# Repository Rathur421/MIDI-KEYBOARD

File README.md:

# 🎹 ARDUINO UNO BASED MIDI KEYBOARD WITH VELOCITY V0.1

The documentation of the code is currently being made as well as the code improved.

This project use the [Arduino MIDI Library](https://github.com/FortySevenEffects/arduino_midi_library)

:warning: the easiest way will always be to buy a midi-keyboard

Up to 88 Key(and more if needed) currently tested for 61 key without major issues.

This github repo is made to propose some (I hope) helpfull ressources to make a MIDI Keyboard wich take in charge the velocity using an arduino-uno and some multiplexer(74HC4051). This my first:

- ARDUINO based project.
- [ARDUINO library](https://github.com/Rathur421/MIDI-KEYBOARD/tree/Master/PCB/circuit) (and first C++ program).
- [PCB conception](https://github.com/Rathur421/MIDI-KEYBOARD/tree/Master/Arduino_Code/lib).

so please try to not be too rude.

The file for the arduino shield conception are [here](https://github.com/Rathur421/MIDI-KEYBOARD/tree/Master/PCB/circuit). The file were created using [Kicad](https://kicad.org/).

## How the shield works

The number of pin on an arduino is clearly not sufficient to plug directly a keyboard matrice of a large keyboard so the idea is to use some multiplexer/demultiplexer to help us.

The biggest problem of this basic idea is that the more key you had the longueur will be the execution of the loop and the less precise will be the velocity.

we use only 1 demultiplexer `READMUX` and up to 3 multiplexer `WRITE_MUX`.
They are globally define in the code ([here](https://github.com/Rathur421/MIDI-KEYBOARD/blob/Master/Arduino_Code/lib/VeloceKey/src/VeloceKey.cpp) line 4 and 6) as they are dependent of the architecture of the project.

The switch between the different multiplexer is made by activating the pin to which each of the multiplexer is link in the PCB(from pin 11 to 13 of the arduino uno board) in the [main] program (from line 23 to 30).

## How the code works

You need to initialise all the key of your actual keyboard and put it in an array as in [main][main] from line 60 and 130.

Then you update all the key and check if the state changed based on the method `YOUR_VELOCEKEY.getKeyChanged()`.
If the state changed you can do the following:

- If it is in state 2 you can send a `MIDI.sendNoteOn(YOUR_VELOCEKEY.getNote(), YOUR_VELOCEKEY.getVelocity(), 1);`.
- If it is in state 3 you can send a `MIDI.sendNoteOff(YOUR_VELOCEKEY.getNote(), YOUR_VELOCEKEY.getVelocity(), 1);`.

That is made in the function update in [main][main] from line 20 to 58.

The code use principally the library [VeloceKey](###well-how-does-the-veloceKey-library-works)

### Well how does the VeloceKey library works?

This library is made to be intuitive for the user as each physical key of the keyboard correspond to a VeloceKey object in the program.

The VeloceKey object is built around a state byte to take the less place possible of the 2kB of RAM available on the Arduino Uno.

| bit position | 7        | 6        | 5                    | 4                    | 3              | 2                       | 1          | 0                   |
| ------------ | -------- | -------- | -------------------- | -------------------- | -------------- | ----------------------- | ---------- | ------------------- |
| used for     | not used | not used | Key previous state 1 | Key previous state 2 | velocity state | velocity previous state | main state | main previous state |

The key of a midi keyboard is composed of two push button, the main and velocity button each one have his `actual` and `previous state` stored inside the `state byte`.

When the programme loop the `state byte` [update](####Update) and if the `previous state` doesn't match with the `actual state` then the `key state` will be changed.

#### Key state

The `key state` can be accessed via the method `YOUR_VELOCEKEY.getKeyState()` which return a byte between 0 and 3 which stand for:

- 0: Key not pressed
- 1: Key currently pressed
- 2: Key pressed
- 3: Key released

The `key state` is not directly stored inside the `byte state` as it can be deduced of the `key previous state` and the `velocity` and `main state`

#### Update

The update basically store the `key previous state` and replace the `previous state` by the `actual state` before storing the `new state` in the `actual state` if necessary.

If the `state` just passed to 1 the time is registered inside the `veloceKey` object.

If the `state` just passed to 2 the timer is used to store the velocity inside the `veloceKey` object and can be accessed with `YOUR_VELOCEKEY.getVelocity()`.

[main]: https://github.com/Rathur421/MIDI-KEYBOARD/blob/Master/Arduino_Code/src/main.cpp

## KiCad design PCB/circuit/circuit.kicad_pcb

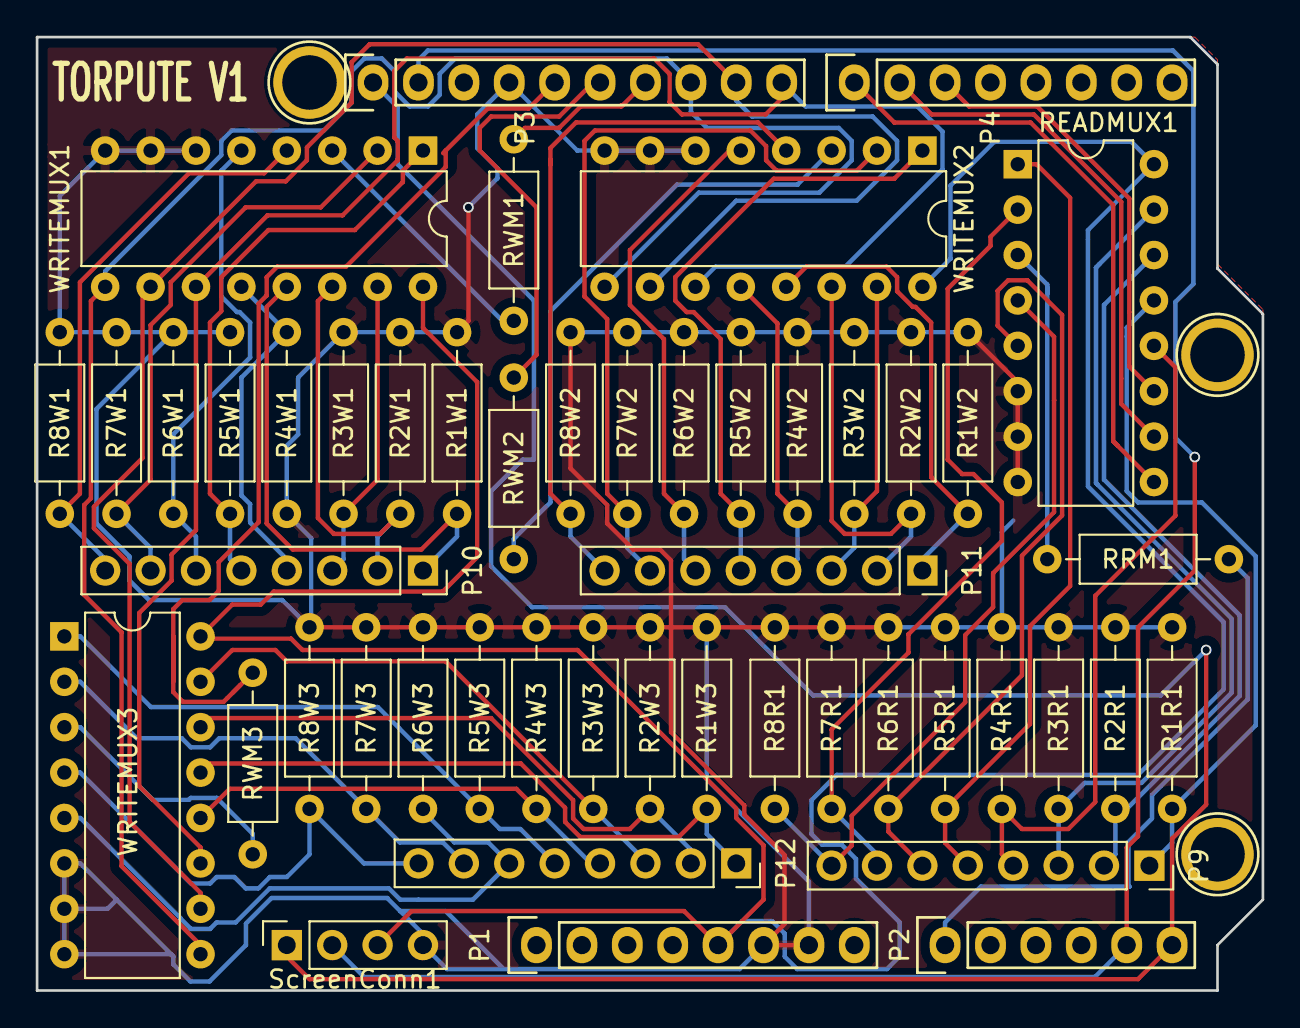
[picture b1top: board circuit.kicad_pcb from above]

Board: 2 copper layers, 68.6 x 53.3 mm, 52 parts (0 on the bottom side), 50 nets.

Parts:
P1: Power; Socket_Strip_Arduino_1x08
P2: Analog; Socket_Strip_Arduino_1x06
P3: Digital; Socket_Strip_Arduino_1x10
P4: Digital; Socket_Strip_Arduino_1x08
P6, P7, P8: CONN_01X01; Arduino_1pin
P9: ReadMuxconn; PinSocket_1x08_P2.54mm_Vertical
P10: WriteMux1conn; PinSocket_1x08_P2.54mm_Vertical
P11: WriteMux2conn; PinSocket_1x08_P2.54mm_Vertical
P12: WriteMux3conn; PinSocket_1x08_P2.54mm_Vertical
R1R1, R1W1, R1W2, R1W3, R2R1, R2W1, R2W2, R2W3, R3R1, R3W1, R3W2, R3W3, R4R1, R4W1, R4W2, R4W3, R5R1, R5W1, R5W2, R5W3, R6R1, R6W1, R6W2, R6W3, R7R1, R7W1, R7W2, R7W3, R8R1, R8W1, R8W2, R8W3: 47K; R_Axial_DIN0207_L6.3mm_D2.5mm_P10.16mm_Horizontal
READMUX1: 74HC4051; DIP-16_W7.62mm
RRM1: R; R_Axial_DIN0207_L6.3mm_D2.5mm_P10.16mm_Horizontal
RWM1, RWM2, RWM3: R; R_Axial_DIN0207_L6.3mm_D2.5mm_P10.16mm_Horizontal
ScreenConn1: Conn_01x04; PinSocket_1x04_P2.54mm_Vertical
WRITEMUX1, WRITEMUX2, WRITEMUX3: 74HC4051; DIP-16_W7.62mm

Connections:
+5V: P1.5, READMUX1.16, ScreenConn1.3, WRITEMUX1.16, WRITEMUX2.16, WRITEMUX3.16
/5(**): P4.3, READMUX1.11
/6(**): P4.2, READMUX1.10
/7: P4.1, READMUX1.9
/8: P3.10, WRITEMUX1.11, WRITEMUX2.11, WRITEMUX3.11
/9(**): P3.9, WRITEMUX1.10, WRITEMUX2.10, WRITEMUX3.10
/10(**/SS): P3.8, WRITEMUX1.9, WRITEMUX2.9, WRITEMUX3.9
/11(**/MOSI): P3.7, RWM1.2
/12(MISO): P3.6, RWM2.2
/13(SCK): P3.5, RWM3.2
/A0: P2.1, RRM1.2
/A4(SDA): P2.5, P3.2, ScreenConn1.2
/A5(SCL): P2.6, P3.1, ScreenConn1.1
GND: P1.6, P1.7, P3.4, R1R1.1, R1W1.1, R1W2.1, R1W3.1, R2R1.1, R2W1.1, R2W2.1, R2W3.1, R3R1.1, R3W1.1, R3W2.1, R3W3.1, R4R1.1, R4W1.1, R4W2.1, R4W3.1, R5R1.1, R5W1.1, R5W2.1, R5W3.1, R6R1.1, R6W1.1, R6W2.1, R6W3.1, R7R1.1, R7W1.1, R7W2.1, R7W3.1, R8R1.1, R8W1.1, R8W2.1, R8W3.1, READMUX1.6, READMUX1.7, READMUX1.8, ScreenConn1.4, WRITEMUX1.6, WRITEMUX1.7, WRITEMUX1.8, WRITEMUX2.6, WRITEMUX2.7, WRITEMUX2.8, WRITEMUX3.6, WRITEMUX3.7, WRITEMUX3.8
unnamed: P9.1, R1R1.2, READMUX1.13
unnamed: P9.2, R2R1.2, READMUX1.14
unnamed: P9.3, R3R1.2, READMUX1.15
unnamed: P9.4, R4R1.2, READMUX1.12
unnamed: P9.5, R5R1.2, READMUX1.1
unnamed: P9.6, R6R1.2, READMUX1.5
unnamed: P9.7, R7R1.2, READMUX1.2
unnamed: P9.8, R8R1.2, READMUX1.4
unnamed: P10.1, R1W1.2, WRITEMUX1.13
unnamed: P10.2, R2W1.2, WRITEMUX1.14
unnamed: P10.3, R3W1.2, WRITEMUX1.15
unnamed: P10.4, R4W1.2, WRITEMUX1.12
unnamed: P10.5, R5W1.2, WRITEMUX1.1
unnamed: P10.6, R6W1.2, WRITEMUX1.5
unnamed: P10.7, R7W1.2, WRITEMUX1.2
unnamed: P10.8, R8W1.2, WRITEMUX1.4
unnamed: P11.1, R1W2.2, WRITEMUX2.13
unnamed: P11.2, R2W2.2, WRITEMUX2.14
unnamed: P11.3, R3W2.2, WRITEMUX2.15
unnamed: P11.4, R4W2.2, WRITEMUX2.12
unnamed: P11.5, R5W2.2, WRITEMUX2.1
unnamed: P11.6, R6W2.2, WRITEMUX2.5
unnamed: P11.7, R7W2.2, WRITEMUX2.2
unnamed: P11.8, R8W2.2, WRITEMUX2.4
unnamed: P12.1, R1W3.2, WRITEMUX3.13
unnamed: P12.2, R2W3.2, WRITEMUX3.14
unnamed: P12.3, R3W3.2, WRITEMUX3.15
unnamed: P12.4, R4W3.2, WRITEMUX3.12
unnamed: P12.5, R5W3.2, WRITEMUX3.1
unnamed: P12.6, R6W3.2, WRITEMUX3.5
unnamed: P12.7, R7W3.2, WRITEMUX3.2
unnamed: P12.8, R8W3.2, WRITEMUX3.4
unnamed: READMUX1.3, RRM1.1
unnamed: RWM1.1, WRITEMUX1.3
unnamed: RWM2.1, WRITEMUX2.3
unnamed: RWM3.1, WRITEMUX3.3

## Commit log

2020-11-19 Starting of the git repo
2020-11-19 Add description
2020-11-19 Delete Description.md
    fail 01
2020-11-19 Add README
2020-11-19 README UPDATE
2020-11-19 little update
2020-11-19 Image
2020-11-19 Added circuit and Image to readme
2020-11-19 change title readme
